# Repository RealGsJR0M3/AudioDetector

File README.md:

git add .
git commit -m "message"
git push
git clone

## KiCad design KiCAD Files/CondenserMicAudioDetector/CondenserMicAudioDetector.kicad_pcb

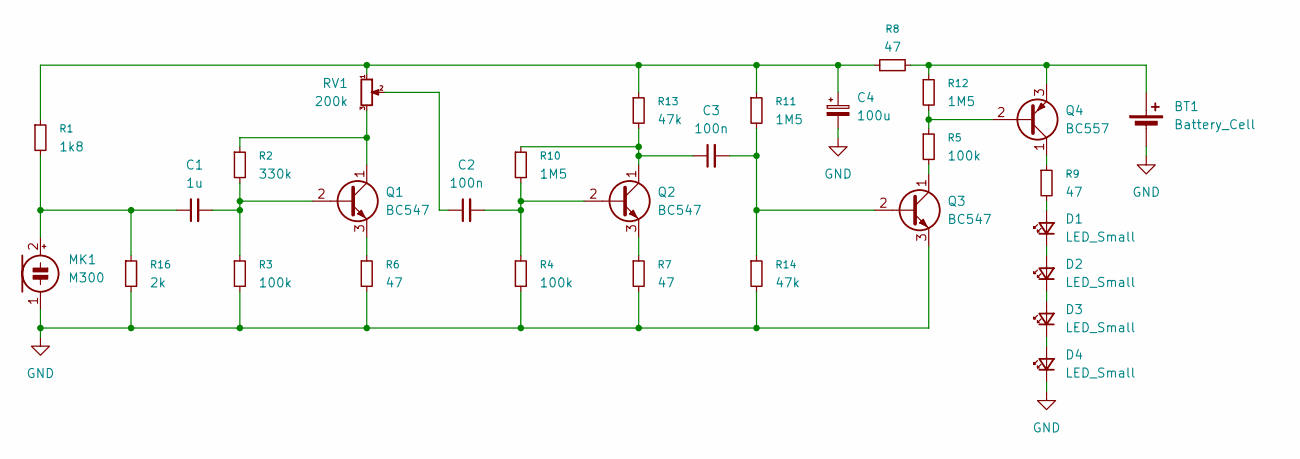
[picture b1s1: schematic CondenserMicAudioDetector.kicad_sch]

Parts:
BT1: Battery_Cell; TerminalBlock_MaiXu_MX126-5.0-02P_1x02_P5.00mm
C1: 1u; C_0805_2012Metric_Pad1.18x1.45mm_HandSolder
C2, C3: 100n; C_0805_2012Metric_Pad1.18x1.45mm_HandSolder
C4: 100u; CP_Radial_D5.0mm_P2.00mm
D1, D2, D3, D4: LED_Small; LED_D5.0mm
MK1: M300; TerminalBlock_MaiXu_MX126-5.0-02P_1x02_P5.00mm
Q1, Q2, Q3: BC547; TO-92_Inline
Q4: BC557; TO-92_Inline
R1: 1k8; R_0805_2012Metric_Pad1.20x1.40mm_HandSolder
R2: 330k; R_0805_2012Metric_Pad1.20x1.40mm_HandSolder
R3, R4, R5: 100k; R_0805_2012Metric_Pad1.20x1.40mm_HandSolder
R6, R7, R8, R9: 47; R_0805_2012Metric_Pad1.20x1.40mm_HandSolder
R10, R11, R12: 1M5; R_0805_2012Metric_Pad1.20x1.40mm_HandSolder
R13, R14: 47k; R_0805_2012Metric_Pad1.20x1.40mm_HandSolder
R16: 2k; R_0805_2012Metric_Pad1.20x1.40mm_HandSolder
RV1: 200k; Potentiometer_Piher_PC-16_Single_Horizontal

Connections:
GND: BT1.2 (-), C4.2, D4.1 (K), MK1.1 (-), Q3.3 (E), R3.2, R4.2, R6.2, R7.2, R14.2, R16.2
unnamed: BT1.1 (+), Q4.3 (E), R8.2, R12.1
unnamed: C2.1, RV1.2
unnamed: C4.1, R1.1, R8.1, R11.1, R13.1, RV1.1
unnamed: D1.2 (A), R9.2
unnamed: D1.1 (K), D2.2 (A)
unnamed: D2.1 (K), D3.2 (A)
unnamed: D3.1 (K), D4.2 (A)
unnamed: C1.1, MK1.2 (+), R1.2, R16.1
unnamed: C1.2, Q1.2 (B), R2.2, R3.1
unnamed: Q1.1 (C), R2.1, RV1.3
unnamed: Q1.3 (E), R6.1
unnamed: C2.2, Q2.2 (B), R4.1, R10.2
unnamed: C3.1, Q2.1 (C), R10.1, R13.2
unnamed: Q2.3 (E), R7.1
unnamed: C3.2, Q3.2 (B), R11.2, R14.1
unnamed: Q3.1 (C), R5.2
unnamed: Q4.2 (B), R5.1, R12.2
unnamed: Q4.1 (C), R9.1

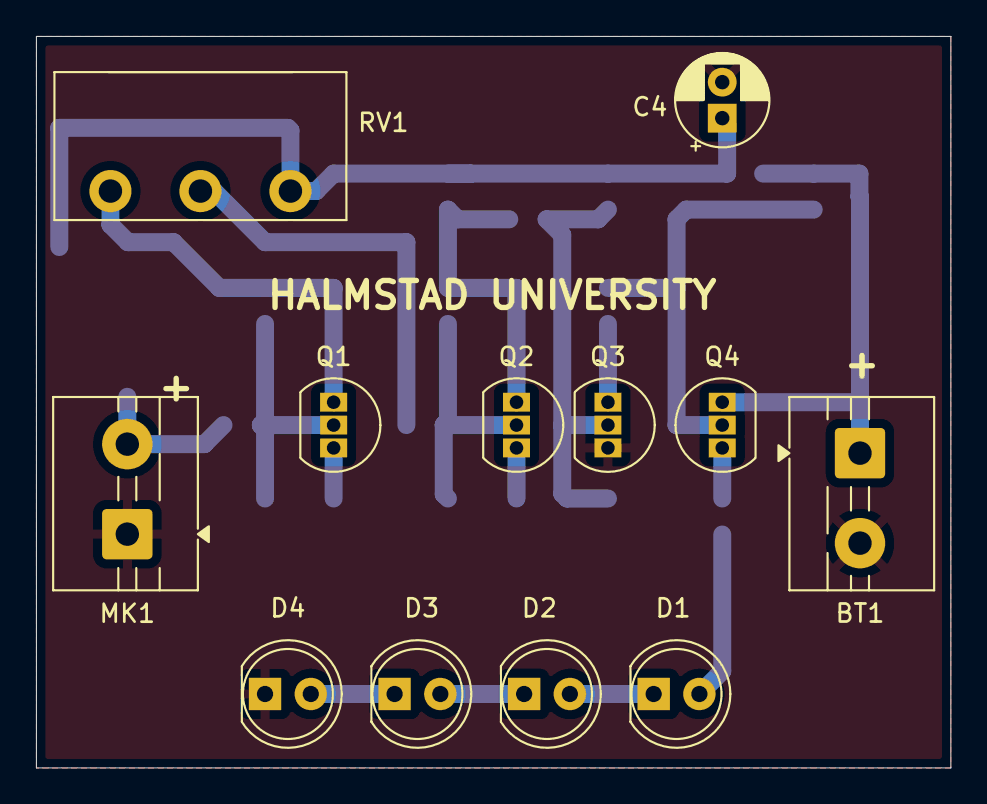
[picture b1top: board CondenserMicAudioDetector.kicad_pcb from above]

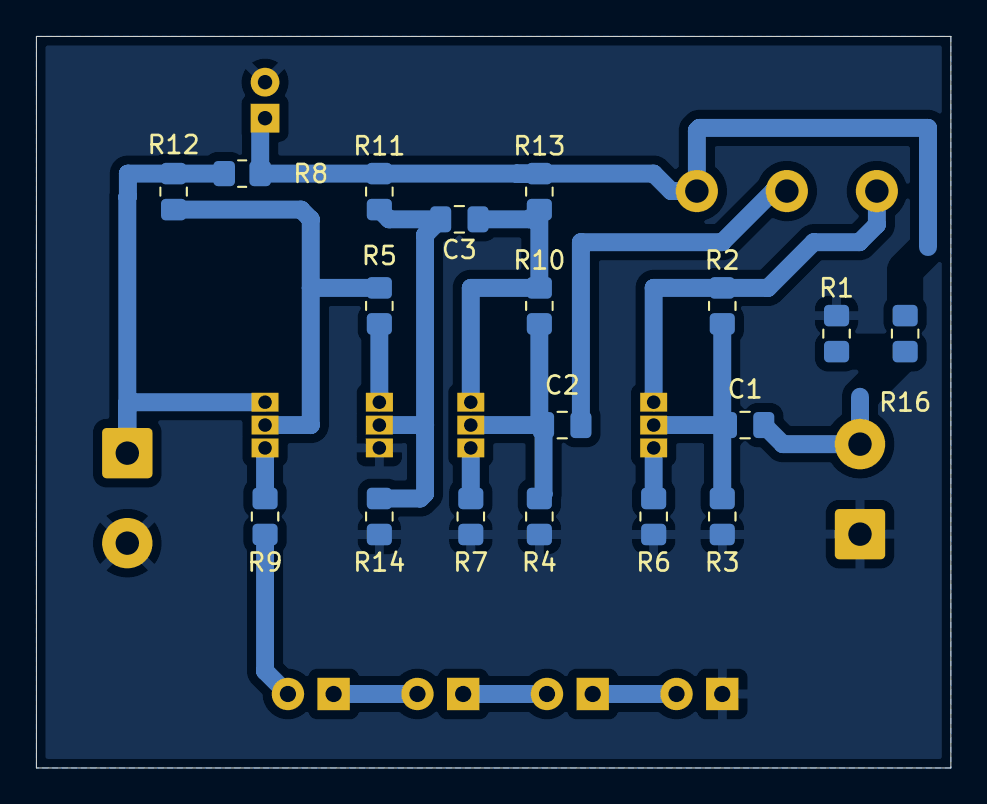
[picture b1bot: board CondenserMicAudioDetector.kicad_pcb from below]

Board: 2 copper layers, 50.8 x 40.6 mm, 30 parts (18 on the bottom side), 19 nets.

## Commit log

2025-04-22 Updated Schematic & PCB Design
2025-04-24 New Folder w/Images of PCB
2025-06-03 Updated Schematic & PCB
2025-06-03 Updated Schematic
2025-06-03 Updated PDF
